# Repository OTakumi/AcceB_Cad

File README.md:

# Accelerometer_Board
https://www.digikey.jp/product-detail/ja/winbond-electronics/W25Q16JVZPIQ/W25Q16JVZPIQ-ND/6193770

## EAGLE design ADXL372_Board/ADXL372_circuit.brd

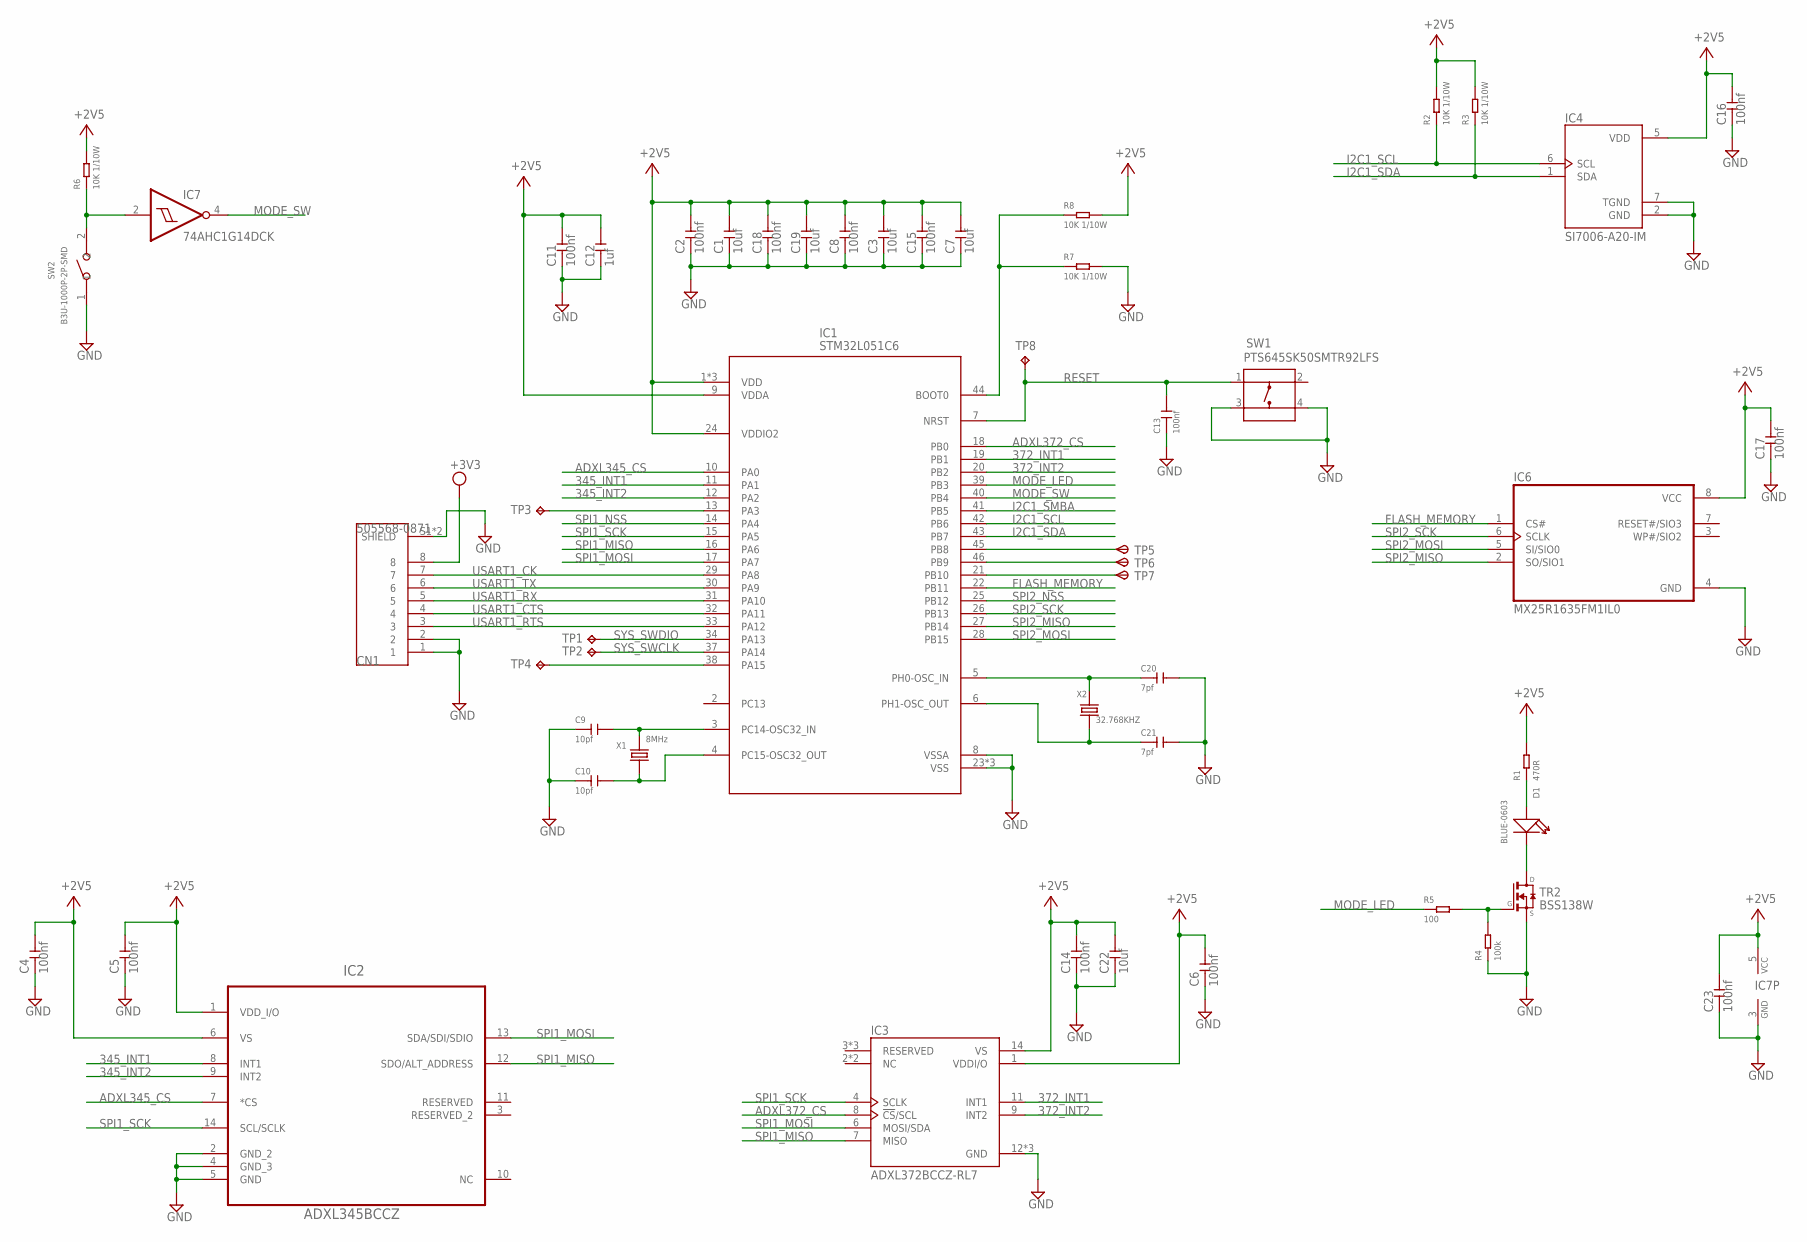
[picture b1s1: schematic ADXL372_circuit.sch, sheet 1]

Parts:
C1, C3, C7, C19, C22: 10uf; C0805
C2, C4, C5, C6, C8, C11, C13, C14, C15, C16, C17, C18, C23: 100nf; C0603
C9, C10: 10pf; C0603
C12: 1uf; C0805
C20, C21: 7pf; C0603
CN1: 505568-0871; MOLEX_505568-0871
D1: BLUE-0603; LED-0603
IC1: STM32L051C6; LQFP48
IC2: ADXL345BCCZ; LGA14R80P3X6_300X500X100
IC3: ADXL372BCCZ-RL7; PQFN50P322X300X114-16N
IC4: SI7006-A20-IM; SON100P300X300X80-7N
IC6: MX25R1635FM1IL0; SOIC127P600X175-8N
IC7: 74AHC1G14DCK; SC70-5
R1: 470R; R0603
R2, R3, R6, R7, R8: 10K 1/10W; R0603
R4: 100k; R0603
R5: 100; R0603
SW1: PTS645SK50SMTR92LFS; SW_PTS645SK50SMTR92LFS
SW2: B3U-1000P-2P-SMD; SW2-2.6-3.0X2.5X1.2+0.4MM
TP1, TP2, TP3, TP4, TP8: TPB1,27; B1,27
TP5, TP6, TP7: TPSB1,27; B1,27
TR2: BSS138W; SOT323-R
X1: 8MHz; X2-SMD-5.0X3.2X1.3MM
X2: 32.768KHZ; X2-SMD-L2.0X1.2X0.55MM

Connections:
345_INT1: IC1.11 (PA1), IC2.8 (INT1)
345_INT2: IC1.12 (PA2), IC2.9 (INT2)
372_INT1: IC1.19 (PB1), IC3.11 (INT1)
372_INT2: IC1.20 (PB2), IC3.9 (INT2)
+2V5: C1.2, C2.2, C3.2, C4.2, C5.2, C6.2, C7.2, C8.2, C11.2, C12.2, C14.2, C15.2, C16.2, C17.2, C18.2, C19.2, C22.2, C23.2, IC1.1 (VDD), IC1.9 (VDDA), IC1.24 (VDDIO2), IC1.36 (VDD), IC1.48 (VDD), IC2.1 (VDD_I/O), IC2.6 (VS), IC3.1 (VDDI/O), IC3.14 (VS), IC4.5 (VDD), IC6.8 (VCC), IC7.5 (VCC), R1.2, R2.2, R3.2, R6.2, R8.2; also elsewhere on the board
+3V3: CN1.8; also elsewhere on the board
ADXL345_CS: IC1.10 (PA0), IC2.7 (*CS)
ADXL372_CS: IC1.18 (PB0), IC3.8 (!CS!/SCL)
FLASH_MEMORY: IC1.22 (PB11), IC6.1 (CS#)
GND: C1.1, C2.1, C3.1, C4.1, C5.1, C6.1, C7.1, C8.1, C9.1, C10.1, C11.1, C12.1, C13.1, C14.1, C15.1, C16.1, C17.1, C18.1, C19.1, C20.2, C21.2, C22.1, C23.1, CN1.1, CN1.2, CN1.S1 (SHIELD), CN1.S2 (SHIELD), IC1.8 (VSSA), IC1.23 (VSS), IC1.35 (VSS), IC1.47 (VSS), IC2.2 (GND_2), IC2.4 (GND_3), IC2.5 (GND), IC3.12 (GND), IC3.13 (GND), IC3.16 (GND), IC4.2 (GND), IC4.7 (TGND), IC6.4 (GND), IC7.3 (GND), R4.1, R7.2, SW1.3, SW1.4, SW2.1, TR2.2 (S); also elsewhere on the board
I2C1_SCL: IC1.42 (PB6), IC4.6 (SCL), R2.1
I2C1_SDA: IC1.43 (PB7), IC4.1 (SDA), R3.1
I2C1_SMBA: IC1.41 (PB5)
MODE_LED: IC1.39 (PB3), R5.1
MODE_SW: IC1.40 (PB4), IC7.4 (O)
unnamed: C9.2, IC1.3 (PC14-OSC32_IN), X1.2
unnamed: C10.2, IC1.4 (PC15-OSC32_OUT), X1.1
unnamed: R4.2, R5.2, TR2.1 (G)
unnamed: IC7.2 (I), R6.1, SW2.2
unnamed: IC1.13 (PA3), TP3.TP
unnamed: IC1.38 (PA15), TP4.TP
unnamed: IC1.44 (BOOT0), R7.1, R8.1
unnamed: C20.1, IC1.5 (PH0-OSC_IN), X2.2
unnamed: C21.1, IC1.6 (PH1-OSC_OUT), X2.1
unnamed: D1.+, R1.1
unnamed: D1.-, TR2.3 (D)
RESET: C13.2, IC1.7 (NRST), SW1.1, TP8.TP
SPI1_MISO: IC1.16 (PA6), IC2.12 (SDO/ALT_ADDRESS), IC3.7 (MISO)
SPI1_MOSI: IC1.17 (PA7), IC2.13 (SDA/SDI/SDIO), IC3.6 (MOSI/SDA)
SPI1_NSS: IC1.14 (PA4)
SPI1_SCK: IC1.15 (PA5), IC2.14 (SCL/SCLK), IC3.4 (SCLK)
SPI2_MISO: IC1.27 (PB14), IC6.2 (SO/SIO1)
SPI2_MOSI: IC1.28 (PB15), IC6.5 (SI/SIO0)
SPI2_NSS: IC1.25 (PB12)
SPI2_SCK: IC1.26 (PB13), IC6.6 (SCLK)
SYS_SWCLK: IC1.37 (PA14), TP2.TP
SYS_SWDIO: IC1.34 (PA13), TP1.TP
TP5: IC1.45 (PB8), TP5.TP
TP6: IC1.46 (PB9), TP6.TP
TP7: IC1.21 (PB10), TP7.TP
USART1_CK: CN1.7, IC1.29 (PA8)
USART1_CTS: CN1.4, IC1.32 (PA11)
USART1_RTS: CN1.3, IC1.33 (PA12)
USART1_RX: CN1.5, IC1.31 (PA10)
USART1_TX: CN1.6, IC1.30 (PA9)

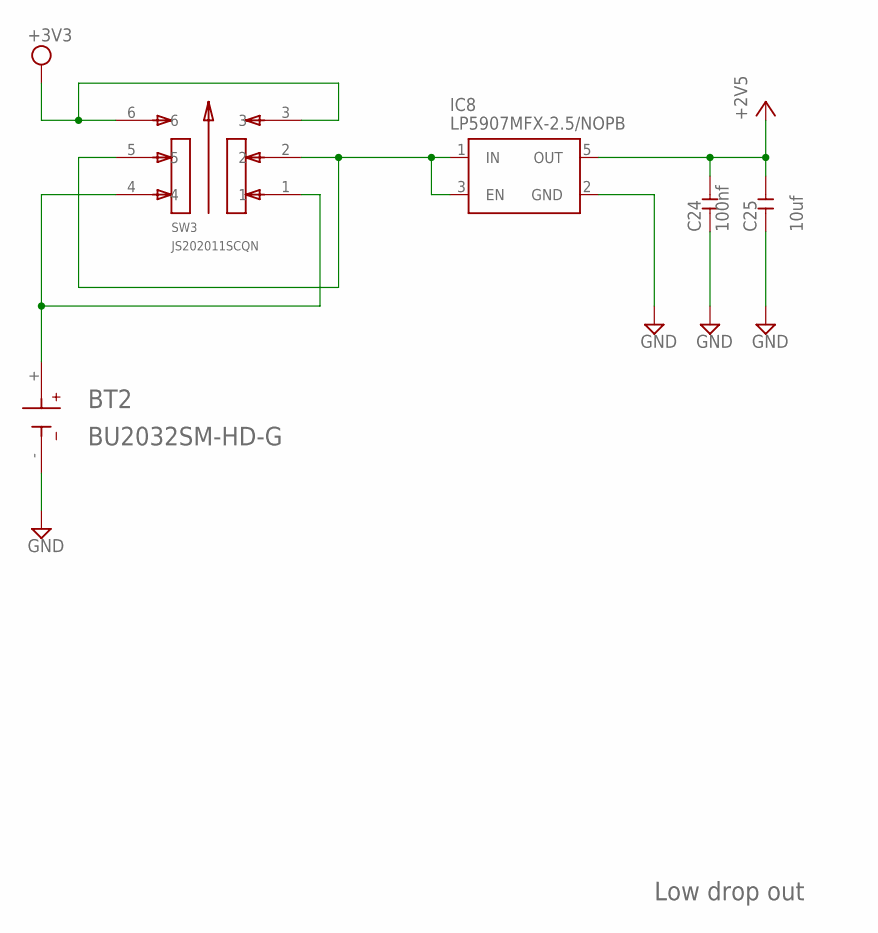
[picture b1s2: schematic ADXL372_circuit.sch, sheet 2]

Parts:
BT2: BU2032SM-HD-G; BAT_BU2032SM-HD-G
C24: 100nf; C0603
C25: 10uf; C0805
IC8: LP5907MFX-2.5/NOPB; SOT95P280X145-5N
SW3: JS202011SCQN; SW_JS202011SCQN

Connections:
+2V5: C24.2, C25.2, IC8.5 (OUT); also elsewhere on the board
+3V3: SW3.3, SW3.6; also elsewhere on the board
+BAT: BT2.+, SW3.1, SW3.4
+VIN: IC8.1 (IN), IC8.3 (EN), SW3.2, SW3.5
GND: BT2.-, C24.1, C25.1, IC8.2 (GND); also elsewhere on the board

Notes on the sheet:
Low drop out

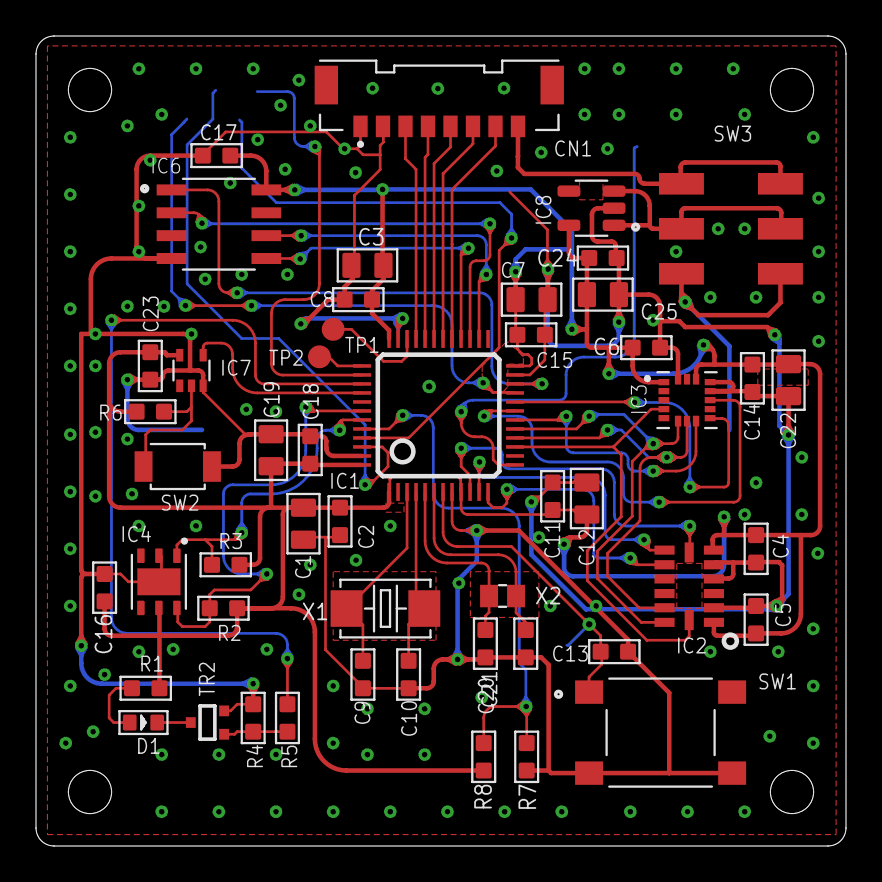
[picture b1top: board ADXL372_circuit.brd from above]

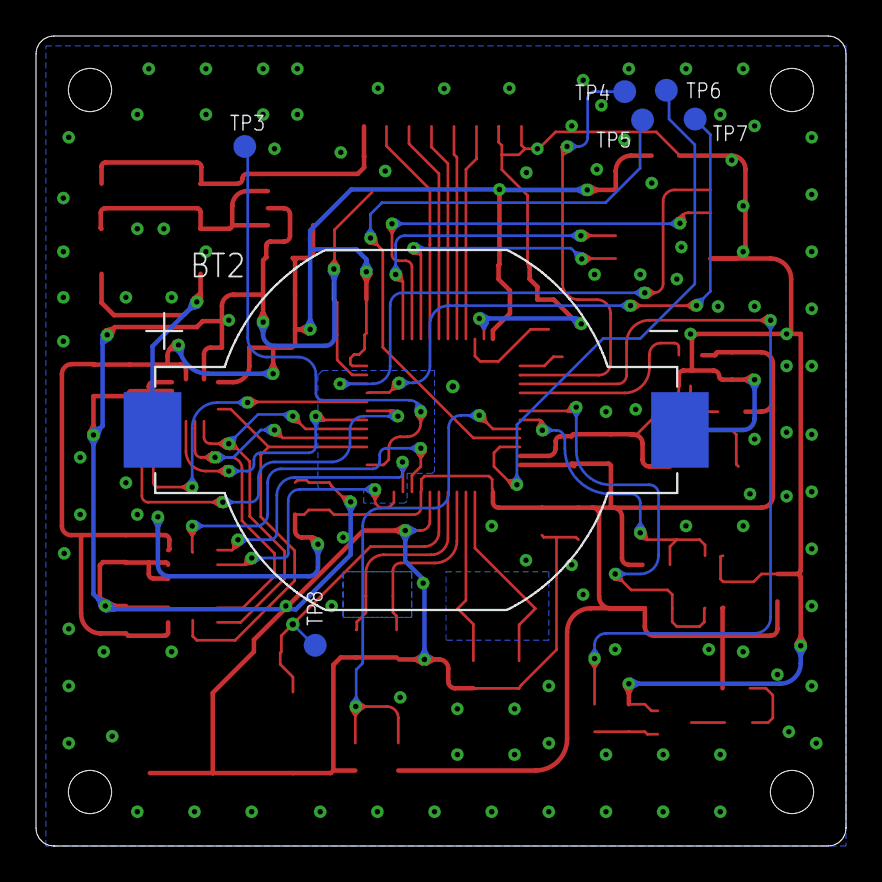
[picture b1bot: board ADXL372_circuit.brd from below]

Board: 2 copper layers, 45.0 x 45.0 mm, 57 parts (7 on the bottom side), 44 nets.

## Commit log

2019-09-28 Add project file and circuit file
2019-09-29 Backlink to CADLAB.io has been added.
2019-09-29 加速度センサーと周辺部品を回路図に追加
2019-09-29 回路図一部修正
2019-10-06 Add Parts
2019-10-07 基板図面を修正
2019-10-07 LED駆動用FETを追加
2019-10-08 パターン図を修正
2019-10-08 回路図修正
2019-10-10 Update circuit
2019-10-20 Update board design
2019-10-23 Add new file
2019-10-23 Update Board design
    Change CN1
2019-10-24 Add Garber data
2019-10-25 Add BOM File
2019-10-25 update BOM
2019-10-31 Correction battery pattern
